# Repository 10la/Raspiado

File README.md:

## Raspiado

A USB hub that fits in the space and footprint of the existing Raspberry Pi.  Compatible with the RPi B, RPi B+, and RPi 2.

Power your Pi, add USB ports, and look great doing it!

******************
### File Descriptions
[4PxU_RPISB Specification.docx](https://github.com/10la/Raspiado/blob/master/4PxU_RPISB%20Specification.docx) is the hardware specification document created by Mindlab Tech for Raspiado.  It represents a formalized document that governs what functions and requirements Raspiado needed and how those things would be achieved.

[PCB Design Files](https://github.com/10la/Raspiado/tree/master/PCB%20Design%20Files) are the EAGLE files for the Raspiado board.

It includes 2 folders- the main design files are in [4PxU_RPi Rev B 18July2014](https://github.com/10la/Raspiado/tree/master/PCB%20Design%20Files/4PxU_RPi%20Rev%20B%2018July2014).  I had a small issue with the board logo and the resulting change are stored in [2014-10-3 new logo](https://github.com/10la/Raspiado/tree/master/PCB%20Design%20Files/2014-10-3%20new%20logo)

When I went to production with Raspiado, I required a few crossreferenced components in order to function with the inventory items that my PCB manufacturer preferred.  You can find those in the [BOM_Crossreferences](https://github.com/10la/Raspiado/blob/master/PCB%20Design%20Files/BOM_Raspiado_V1P4_crossreferences.xlsx) spreadsheet.

******************
### Kickstarter

Raspiado would have never seen the light of day with it's attractive, intelligent, and supportive backers.

When I started the project, I never knew that I'd be able to create something that would be appreciated by people all over the world.

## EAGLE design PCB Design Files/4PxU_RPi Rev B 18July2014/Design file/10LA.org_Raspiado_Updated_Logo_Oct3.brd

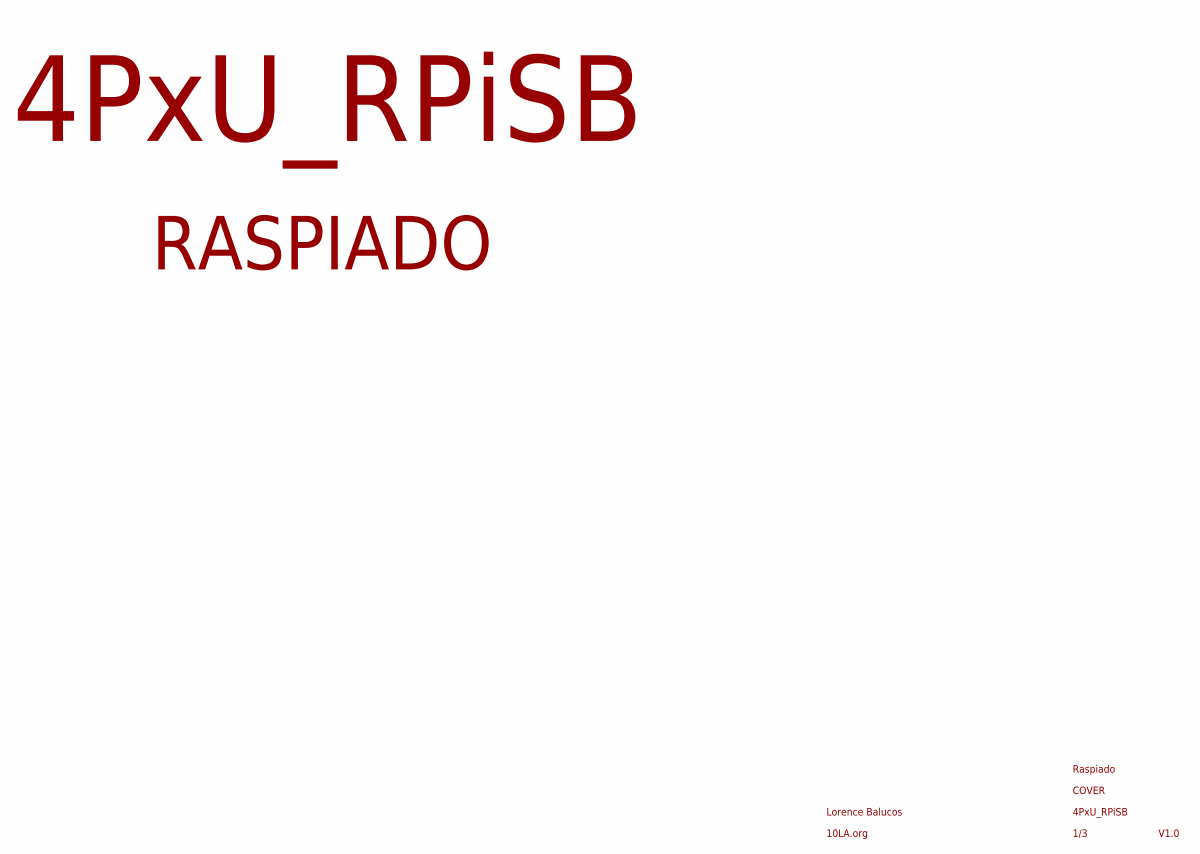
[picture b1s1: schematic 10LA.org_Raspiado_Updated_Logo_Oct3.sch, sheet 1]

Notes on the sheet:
1/3
4PxU_RPiSB
V1.0
10LA.org
RASPIADO
COVER
Lorence Balucos
Raspiado

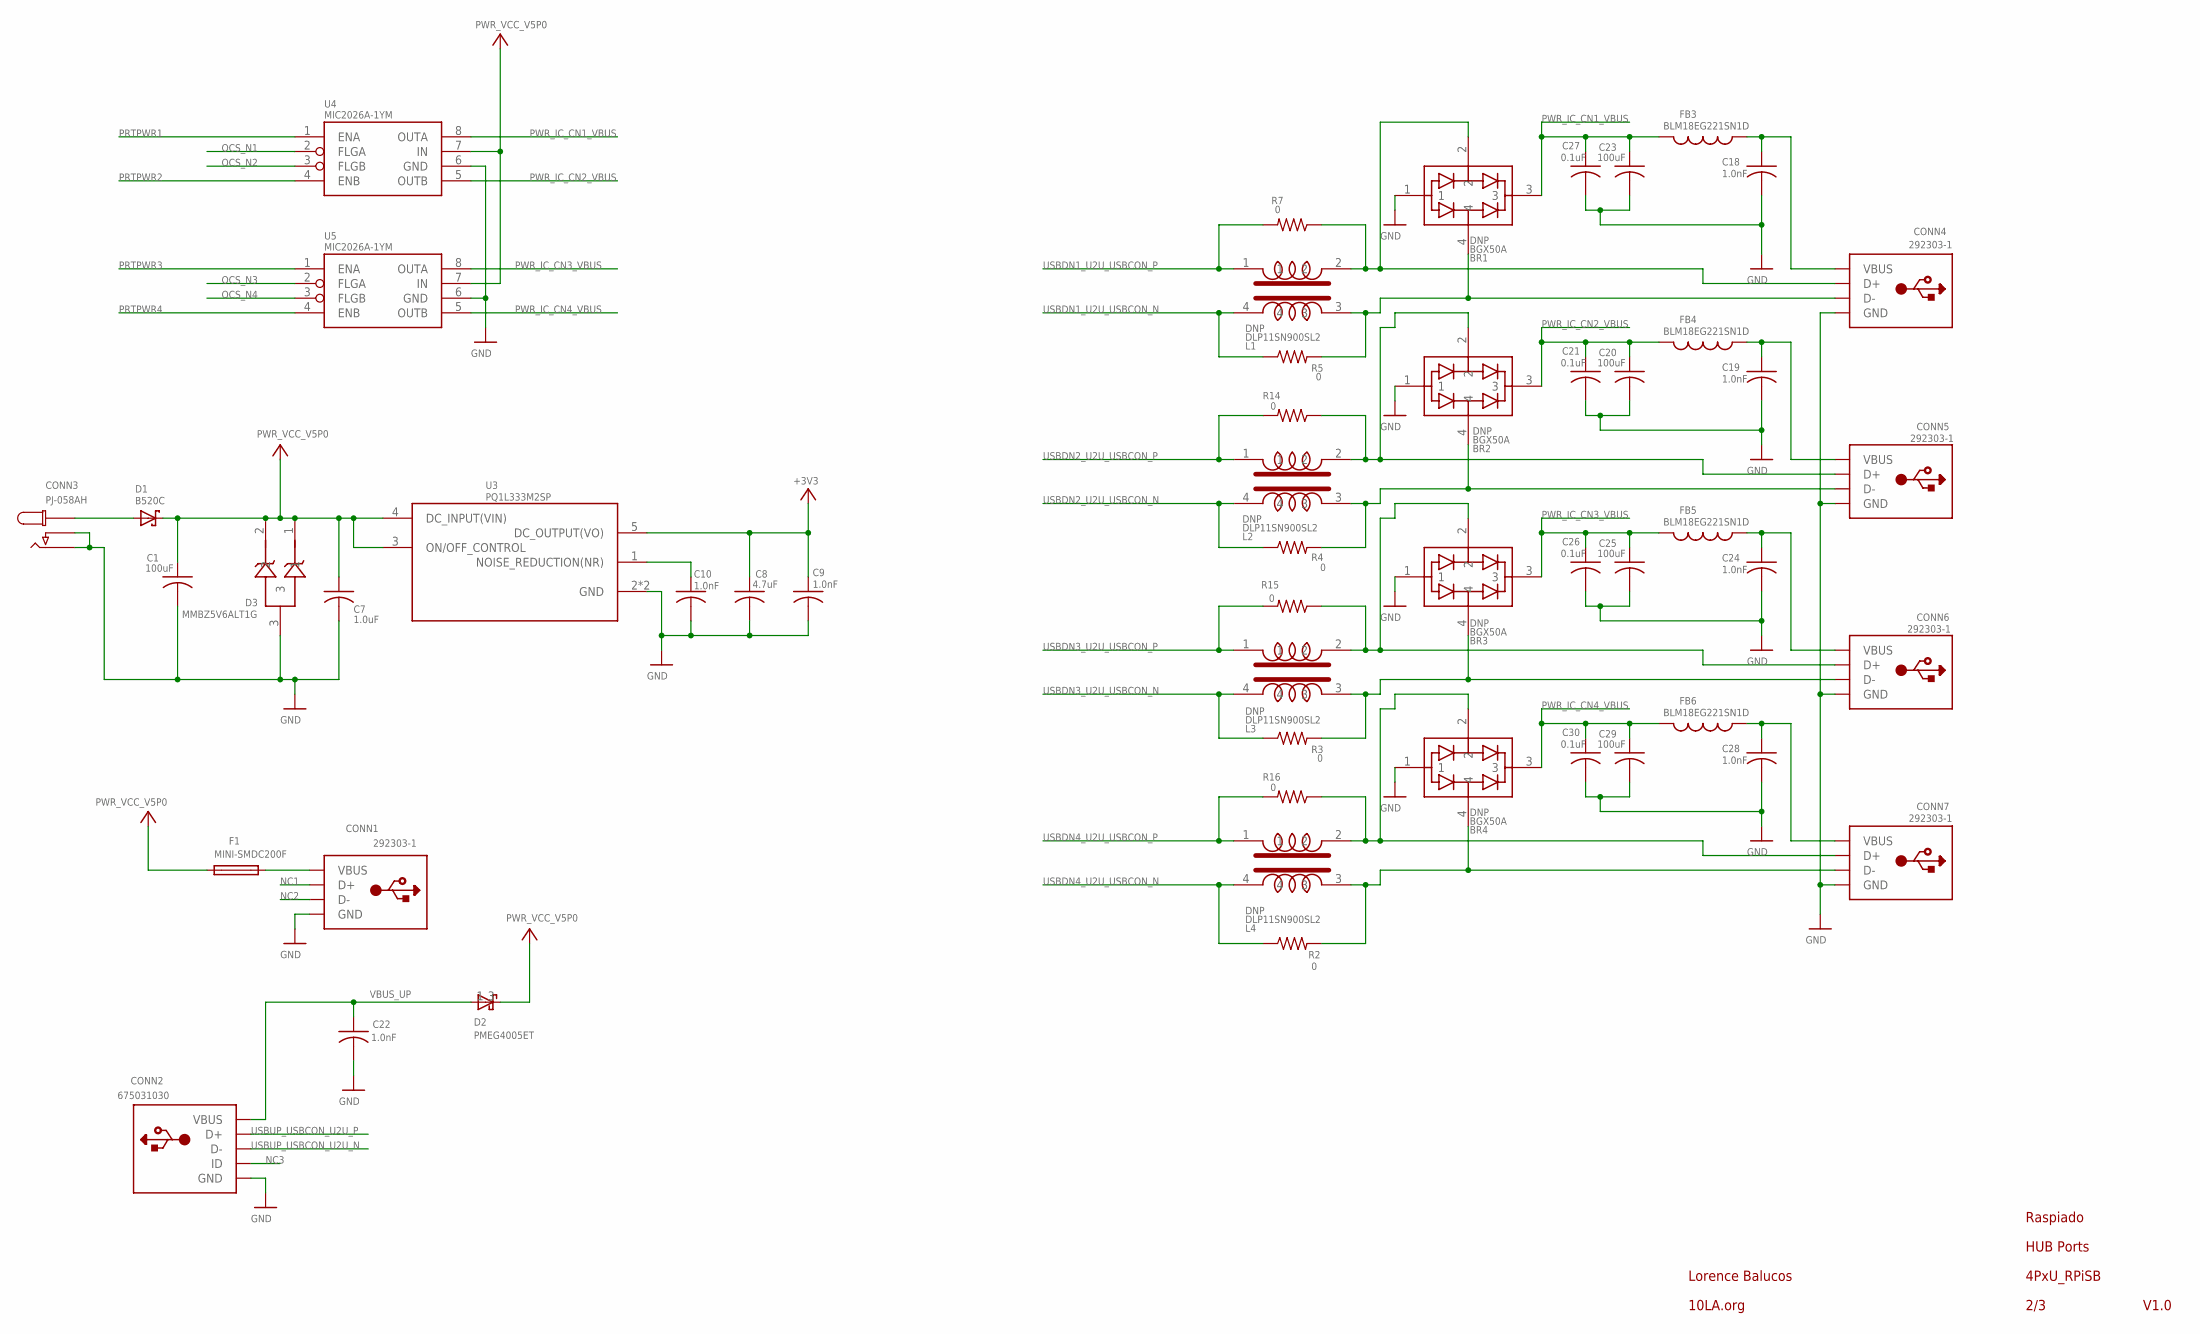
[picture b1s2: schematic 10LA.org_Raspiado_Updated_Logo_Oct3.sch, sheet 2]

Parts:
BR1, BR2, BR3, BR4: BGX50A; SOT-143
C1, C20, C23, C25, C29: 100uF; RADIAL_SMT
C7: 1.0uF; C0603
C8: 4.7uF; C0603
C9, C10, C18, C19, C22, C24, C28: 1.0nF; 0402
C21, C26, C27, C30: 0.1uF; 0402
CONN1, CONN4, CONN5, CONN6, CONN7: 292303-1; STYLEA,RIGHTANGLE,THROUGH-HOLE
CONN2: 675031030; MINI_B
CONN3: PJ-058AH
D1: B520C
D2: PMEG4005ET; SOT23
D3: MMBZ5V6ALT1G; SOT23
F1: MINI-SMDC200F
FB3, FB4, FB5, FB6: BLM18EG221SN1D; C0603
L1, L2, L3, L4: DLP11SN900SL2; 0504
R2, R3, R4, R5, R7, R14, R15, R16: 0; R0402
U3: PQ1L333M2SP
U4, U5: MIC2026A-1YM; SO_08

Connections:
+3V3: C8.1, C9.1, U3.5 (DC_OUTPUT(VO)); also elsewhere on the board
GND: BR1.1, BR2.1, BR3.1, BR4.1, C1.- (2), C7.2, C8.2, C9.2, C10.2, C18.2, C19.2, C20.- (2), C21.2, C22.2, C23.- (2), C24.2, C25.- (2), C26.2, C27.2, C28.2, C29.- (2), C30.2, CONN1.GND, CONN1.GND1 (GND), CONN1.GND2 (GND), CONN2.GND, CONN2.GND1 (GND), CONN2.GND2 (GND), CONN2.GND3 (GND), CONN2.GND4 (GND), CONN3.2, CONN3.3, CONN4.GND, CONN4.GND1 (GND), CONN4.GND2 (GND), CONN5.GND, CONN5.GND1 (GND), CONN5.GND2 (GND), CONN6.GND, CONN6.GND1 (GND), CONN6.GND2 (GND), CONN7.GND, CONN7.GND1 (GND), CONN7.GND2 (GND), D3.3, U3.2 (GND), U3.P$3 (GND), U4.6 (GND), U5.6 (GND); also elsewhere on the board
unnamed: C19.1, CONN5.VBUS, FB4.1
unnamed: BR2.2, CONN5.SIG2 (D+), L2.2, R14.1
unnamed: CONN3.1, D1.P$1 (1)
unnamed: C10.1, U3.1 (NOISE_REDUCTION(NR))
unnamed: C18.1, CONN4.VBUS, FB3.1
unnamed: BR1.2, CONN4.SIG2 (D+), L1.2, R7.1
unnamed: CONN1.VBUS, F1.2
unnamed: C24.1, CONN6.VBUS, FB5.1
unnamed: BR3.2, CONN6.SIG2 (D+), L3.2, R15.1
unnamed: C28.1, CONN7.VBUS, FB6.1
unnamed: BR4.2, CONN7.SIG2 (D+), L4.2, R16.1
NC1: CONN1.SIG2 (D+)
NC2: CONN1.SIG1 (D-)
NC3: CONN2.ID
OCS_N1: U4.2 (FLGA); also elsewhere on the board
OCS_N2: U4.3 (FLGB); also elsewhere on the board
OCS_N3: U5.2 (FLGA); also elsewhere on the board
OCS_N4: U5.3 (FLGB); also elsewhere on the board
PRTPWR1: U4.1 (ENA); also elsewhere on the board
PRTPWR2: U4.4 (ENB); also elsewhere on the board
PRTPWR3: U5.1 (ENA); also elsewhere on the board
PRTPWR4: U5.4 (ENB); also elsewhere on the board
PWR_IC_CN1_VBUS: BR1.3, C23.+ (1), C27.1, FB3.2, U4.8 (OUTA)
PWR_IC_CN2_VBUS: BR2.3, C20.+ (1), C21.1, FB4.2, U4.5 (OUTB)
PWR_IC_CN3_VBUS: BR3.3, C25.+ (1), C26.1, FB5.2, U5.8 (OUTA)
PWR_IC_CN4_VBUS: BR4.3, C29.+ (1), C30.1, FB6.2, U5.5 (OUTB)
USBDN1_U2U_USBCON_N: L1.4, R5.1; also elsewhere on the board
USBDN1_U2U_USBCON_P: L1.1, R7.2; also elsewhere on the board
USBDN1_U2U_USBCON_P2: BR4.4, CONN7.SIG1 (D-), L4.3, R2.2
USBDN1_U2U_USBCON_P3: BR3.4, CONN6.SIG1 (D-), L3.3, R3.2
USBDN1_U2U_USBCON_P4: BR2.4, CONN5.SIG1 (D-), L2.3, R4.2
USBDN1_U2U_USBCON_P5: BR1.4, CONN4.SIG1 (D-), L1.3, R5.2
USBDN2_U2U_USBCON_N: L2.4, R4.1; also elsewhere on the board
USBDN2_U2U_USBCON_P: L2.1, R14.2; also elsewhere on the board
USBDN3_U2U_USBCON_N: L3.4, R3.1; also elsewhere on the board
USBDN3_U2U_USBCON_P: L3.1, R15.2; also elsewhere on the board
USBDN4_U2U_USBCON_N: L4.4, R2.1; also elsewhere on the board
USBDN4_U2U_USBCON_P: L4.1, R16.2; also elsewhere on the board
USBUP_USBCON_U2U_N: CONN2.D-; also elsewhere on the board
USBUP_USBCON_U2U_P: CONN2.D+; also elsewhere on the board
VBUS_UP: C22.1, CONN2.VBUS, D2.1; also elsewhere on the board
VCC: C1.+ (1), C7.1, D1.P$2 (3), D2.3, D3.1, D3.2, F1.1, U3.3 (ON/OFF_CONTROL), U3.4 (DC_INPUT(VIN)), U4.7 (IN), U5.7 (IN)

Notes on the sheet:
2/3
V1.0
Lorence Balucos
10LA.org
Raspiado
4PxU_RPiSB
HUB Ports

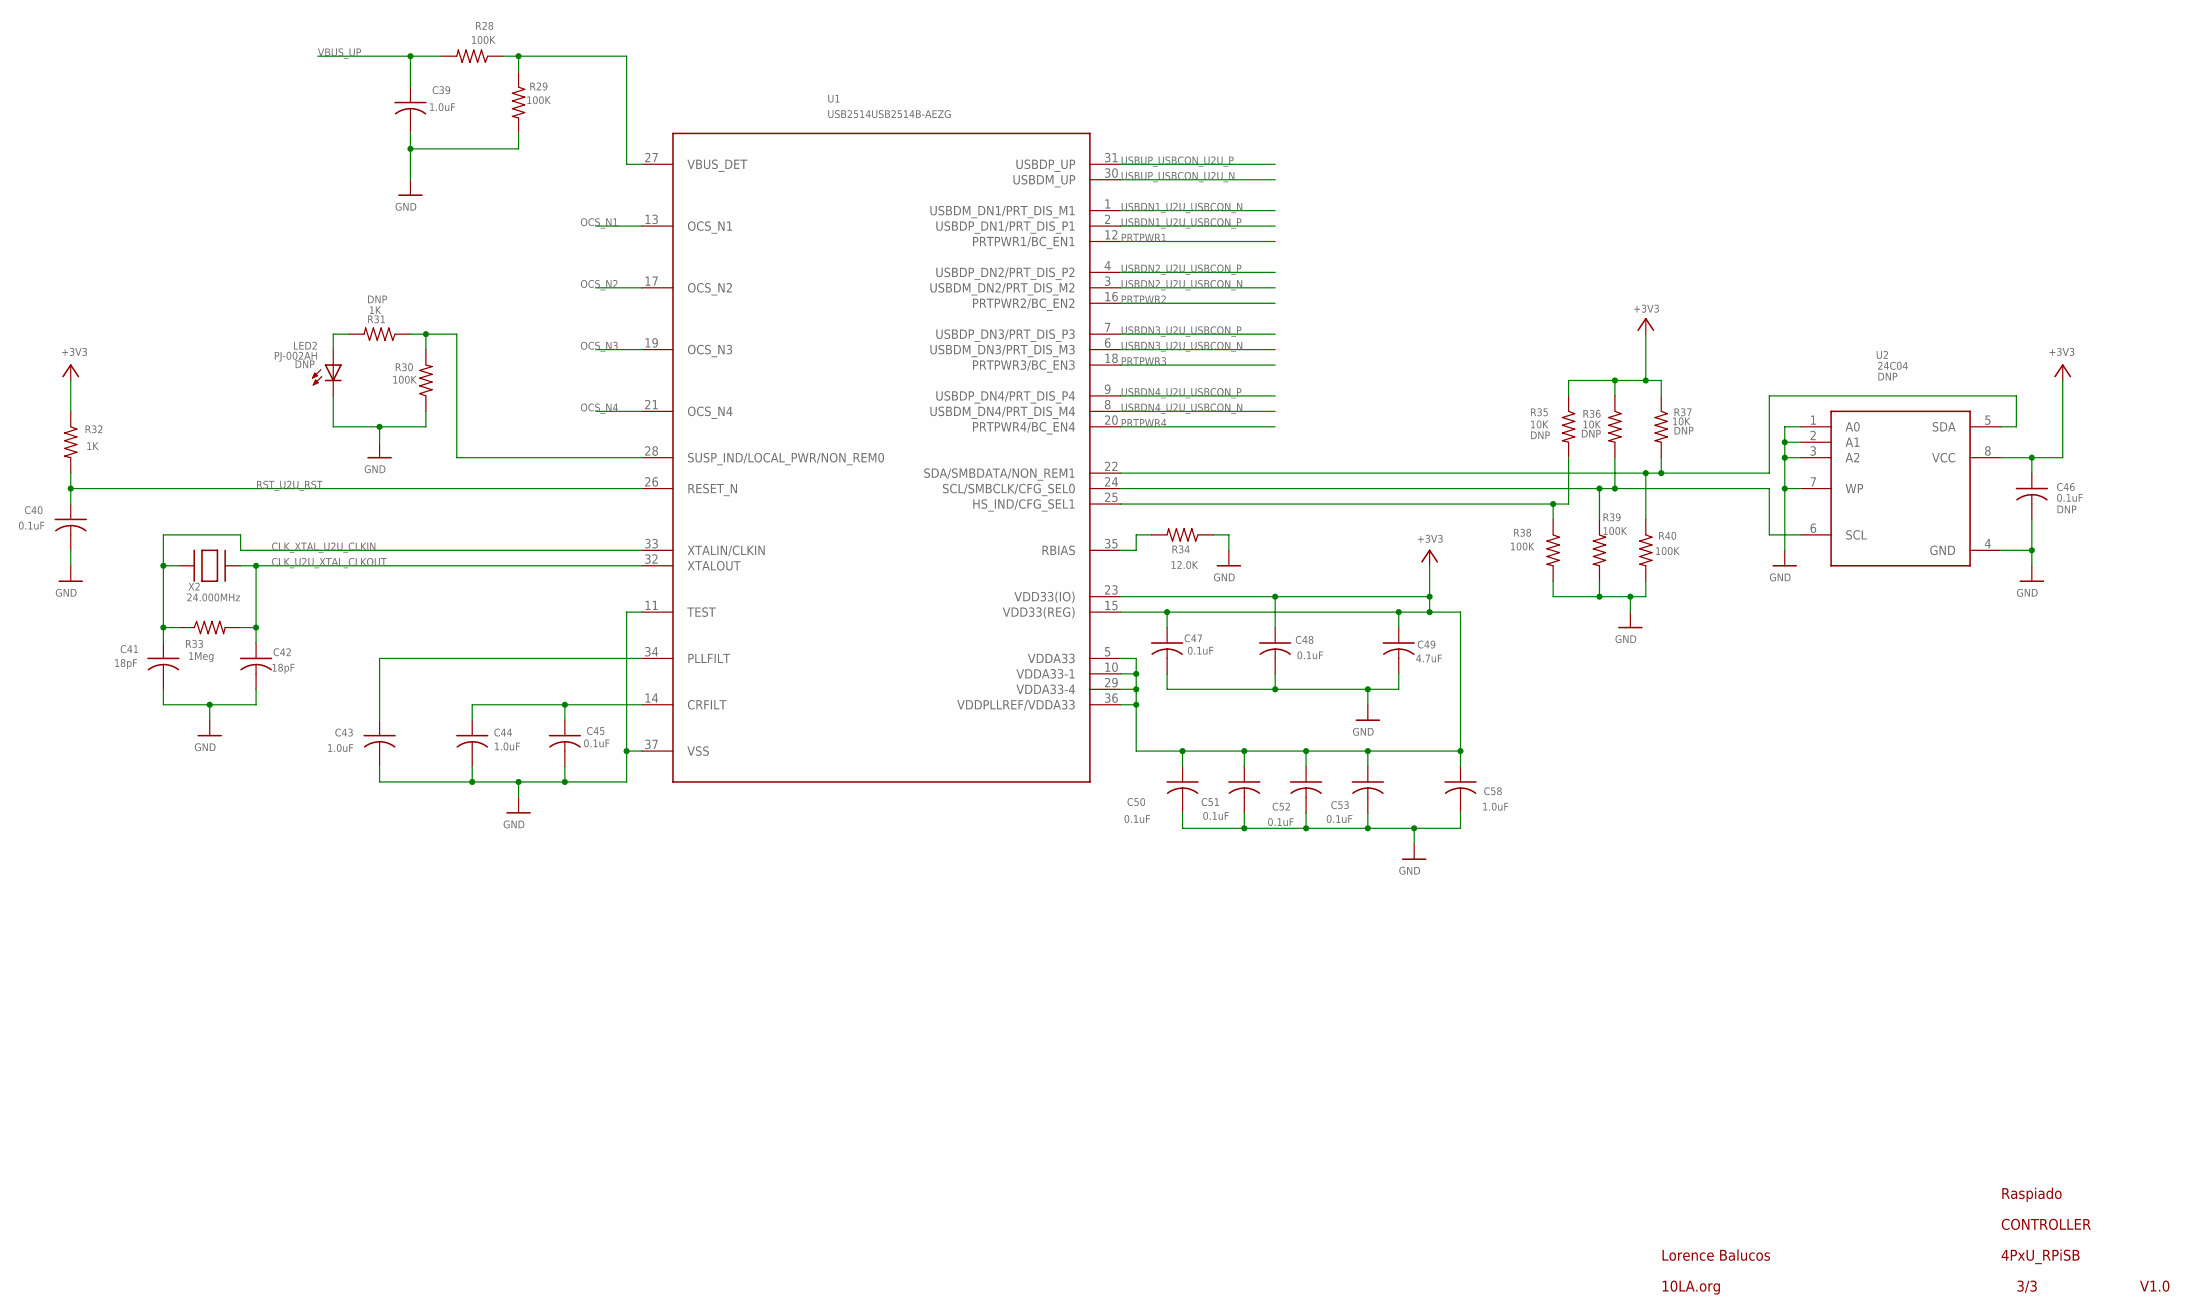
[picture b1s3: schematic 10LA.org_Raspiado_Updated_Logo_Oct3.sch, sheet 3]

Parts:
C39, C58: 1.0uF; C0603
C40, C45, C46, C47, C48, C50, C51, C52, C53: 0.1uF; 0402
C41, C42: 18pF; 0402
C43, C44: 1.0uF; 0402
C49: 4.7uF; C0603
LED2: PJ-002AH; 0603
R28, R29, R30, R38, R39, R40: 100K; R0603
R31, R32: 1K; R0603
R33: 1Meg; R0603
R34: 12.0K; R0603
R35, R36, R37: 10K; R0603
U1: USB2514USB2514B-AEZG; QFN36
U2: 24C04; SO-8
X2: 24.000MHz; HC-49SMT

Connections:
+3V3: C46.1, C47.1, C48.1, C49.1, C50.1, C51.1, C52.1, C53.1, C58.1, R32.1, R35.1, R36.1, R37.1, U1.5 (VDDA33), U1.10 (VDDA33-1), U1.15 (VDD33(REG)), U1.23 (VDD33(IO)), U1.29 (VDDA33-4), U1.36 (VDDPLLREF/VDDA33), U2.8 (VCC); also elsewhere on the board
CLK_U2U_XTAL_CLKOUT: C42.1, R33.2, U1.32 (XTALOUT), X2.2
CLK_XTAL_U2U_CLKIN: C41.1, R33.1, U1.33 (XTALIN/CLKIN), X2.1
CRFILT: C44.1, C45.1, U1.14 (CRFILT)
GND: C39.2, C40.2, C41.2, C42.2, C43.2, C44.2, C45.2, C46.2, C47.2, C48.2, C49.2, C50.2, C51.2, C52.2, C53.2, C58.2, LED2.C, R29.2, R30.1, R34.1, R38.2, R39.2, R40.2, U1.11 (TEST), U1.37 (VSS), U2.1 (A0), U2.2 (A1), U2.3 (A2), U2.4 (GND), U2.7 (WP); also elsewhere on the board
unnamed: LED2.A, R31.2
OCS_N1: U1.13 (OCS_N1); also elsewhere on the board
OCS_N2: U1.17 (OCS_N2); also elsewhere on the board
OCS_N3: U1.19 (OCS_N3); also elsewhere on the board
OCS_N4: U1.21 (OCS_N4); also elsewhere on the board
PLLFILT: C43.1, U1.34 (PLLFILT)
PRTPWR1: U1.12 (PRTPWR1/BC_EN1); also elsewhere on the board
PRTPWR2: U1.16 (PRTPWR2/BC_EN2); also elsewhere on the board
PRTPWR3: U1.18 (PRTPWR3/BC_EN3); also elsewhere on the board
PRTPWR4: U1.20 (PRTPWR4/BC_EN4); also elsewhere on the board
RBIAS: R34.2, U1.35 (RBIAS)
REM0: R30.2, R31.1, U1.28 (SUSP_IND/LOCAL_PWR/NON_REM0)
REM1: R37.2, R40.1, U1.22 (SDA/SMBDATA/NON_REM1), U2.5 (SDA)
RST_U2U_RST: C40.1, R32.2, U1.26 (RESET_N)
SCL: R36.2, R39.1, U1.24 (SCL/SMBCLK/CFG_SEL0), U2.6 (SCL)
SEL1: R35.2, R38.1, U1.25 (HS_IND/CFG_SEL1)
USBDN1_U2U_USBCON_N: U1.1 (USBDM_DN1/PRT_DIS_M1); also elsewhere on the board
USBDN1_U2U_USBCON_P: U1.2 (USBDP_DN1/PRT_DIS_P1); also elsewhere on the board
USBDN2_U2U_USBCON_N: U1.3 (USBDM_DN2/PRT_DIS_M2); also elsewhere on the board
USBDN2_U2U_USBCON_P: U1.4 (USBDP_DN2/PRT_DIS_P2); also elsewhere on the board
USBDN3_U2U_USBCON_N: U1.6 (USBDM_DN3/PRT_DIS_M3); also elsewhere on the board
USBDN3_U2U_USBCON_P: U1.7 (USBDP_DN3/PRT_DIS_P3); also elsewhere on the board
USBDN4_U2U_USBCON_N: U1.8 (USBDM_DN4/PRT_DIS_M4); also elsewhere on the board
USBDN4_U2U_USBCON_P: U1.9 (USBDP_DN4/PRT_DIS_P4); also elsewhere on the board
USBUP_USBCON_U2U_N: U1.30 (USBDM_UP); also elsewhere on the board
USBUP_USBCON_U2U_P: U1.31 (USBDP_UP); also elsewhere on the board
VBUS_UP: C39.1, R28.2; also elsewhere on the board
VBUS_UPSTREAM: R28.1, R29.1, U1.27 (VBUS_DET)

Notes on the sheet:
4PxU_RPiSB
3/3
V1.0
Lorence Balucos
10LA.org
Raspiado
CONTROLLER

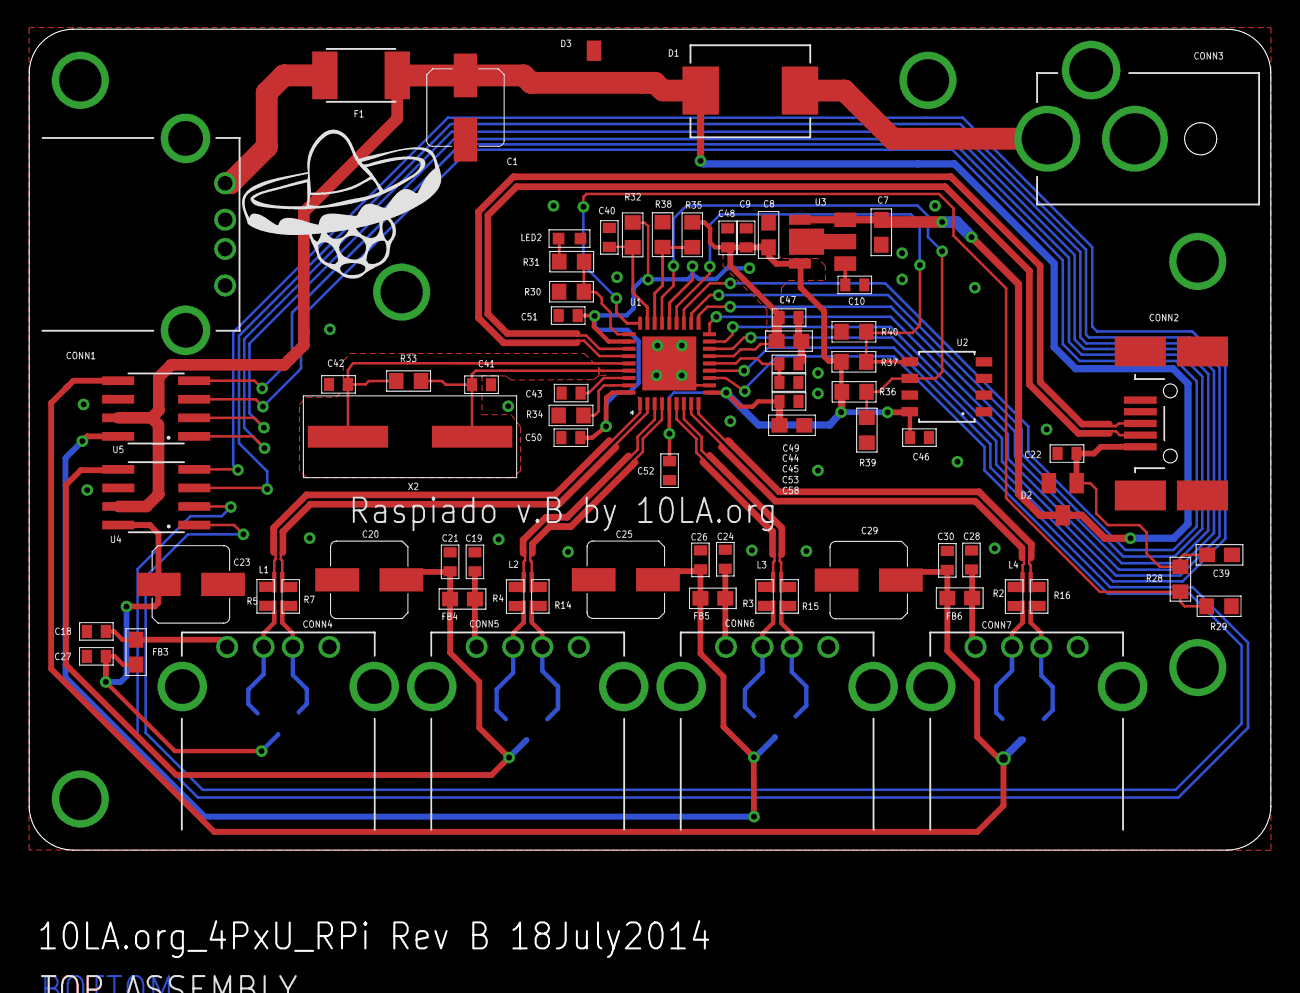
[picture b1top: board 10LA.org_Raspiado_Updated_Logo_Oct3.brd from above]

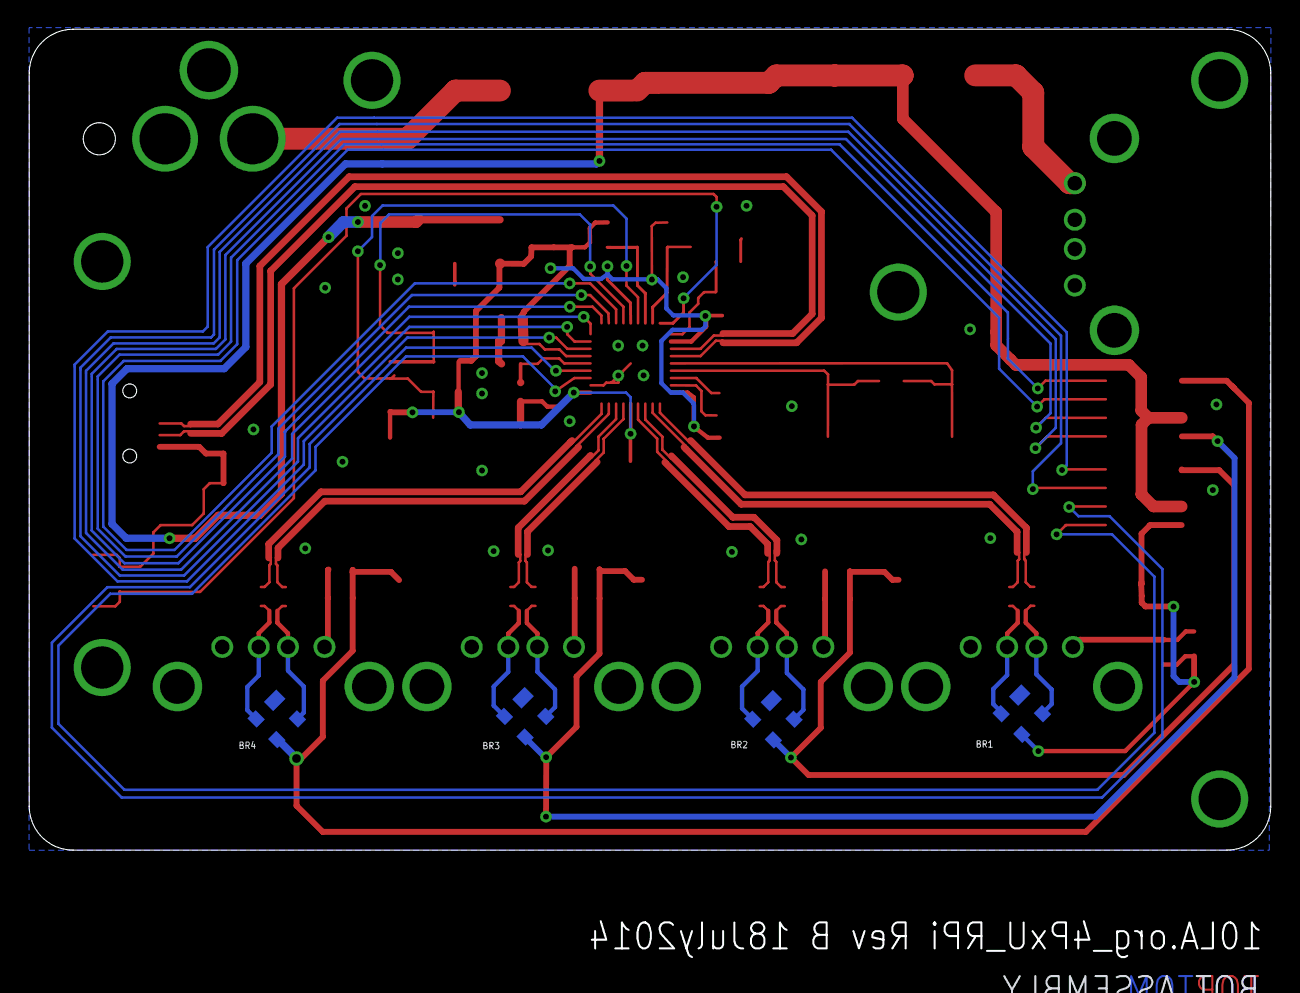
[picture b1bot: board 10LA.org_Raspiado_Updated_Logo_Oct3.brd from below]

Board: 2 copper layers, 85.0 x 56.2 mm, 86 parts (4 on the bottom side), 53 nets.

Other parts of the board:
U$1: FRAME

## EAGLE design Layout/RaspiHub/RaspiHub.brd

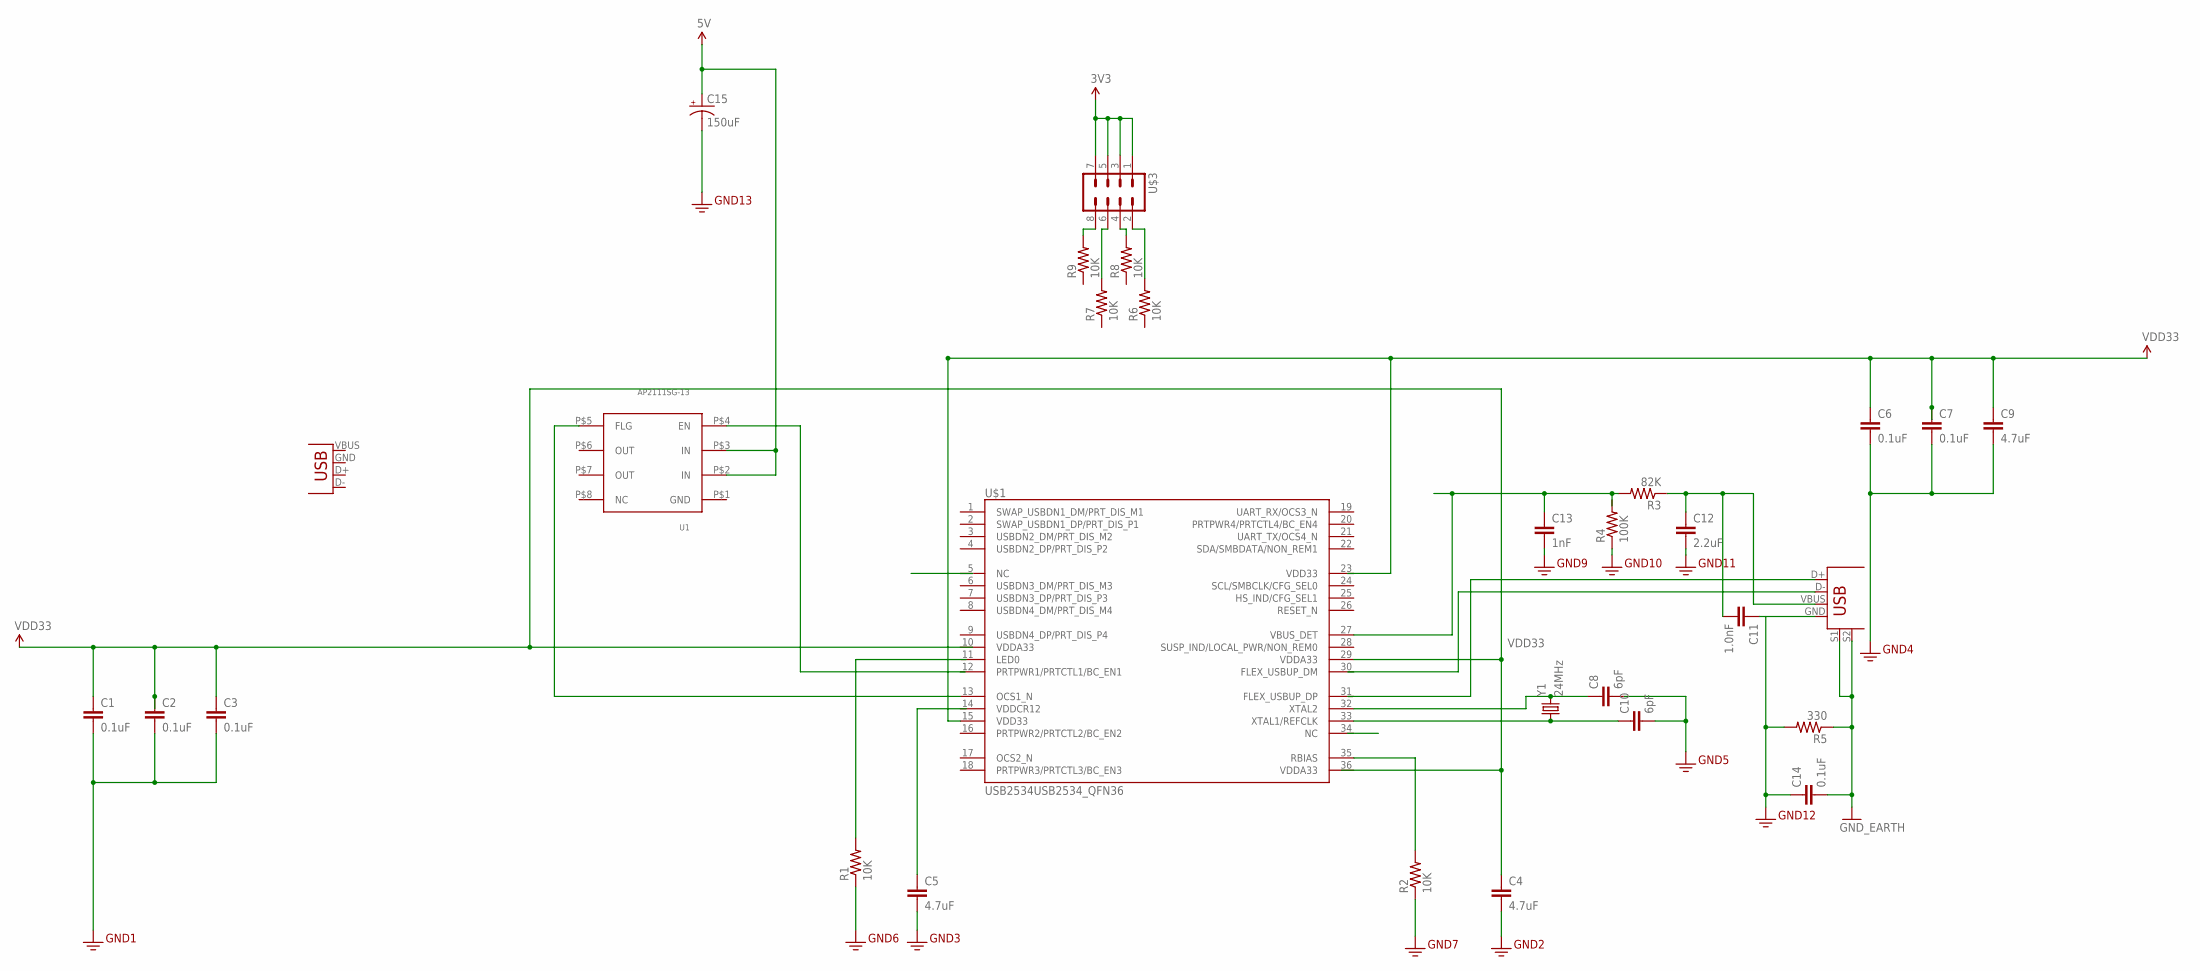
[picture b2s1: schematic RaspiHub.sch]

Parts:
C1, C2, C3, C6, C7: 0.1uF; 0402-CAP
C4, C5, C9: 4.7uF; 0603-CAP
C8, C10: 6pF; 0603-CAP
C11: 1.0nF; 0402-CAP
C12: 2.2uF; 0402-CAP
C13: 1nF; 0402-CAP
C14: 0.1uF; 0603-CAP
C15: 150uF; EIA3528
JP1: USB-A-H
R1, R2, R6, R7, R8, R9: 10K; 0603-RES
R3: 82K; 0603-RES
R4: 100K; 0603-RES
R5: 330; 0603-RES
U1: AP2111SG-13
U$1: USB2534USB2534_QFN36; USB2534
U$2: USB+SHIELD; USB-B-PTH
U$3: M04X2; 2X4
Y1: 24MHz; HC49U-V

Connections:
3.3V: C1.2, C2.2, C3.2, C4.2, C5.2, C6.2, C7.2, C8.2, C9.2, C10.2, C12.2, C13.2, C14.1, C15.C (-), R1.1, R2.1, R4.1, R5.2
GND: C14.2, R5.1, U1.P$1 (GND), U$2.S1, U$2.S2
unnamed: C10.1, U$1.33 (XTAL1/REFCLK), Y1.1
unnamed: C8.1, U$1.32 (XTAL2), Y1.2
unnamed: R2.2, U$1.35 (RBIAS)
unnamed: R7.2, U$3.6
unnamed: C11.2, C12.1, R3.1, U$2.VBUS
unnamed: C11.1, U$2.GND
unnamed: R9.2, U$3.8
unnamed: R8.2, U$3.4
unnamed: R6.2, U$3.2
unnamed: U1.P$5 (FLG), U$1.13 (OCS1_N)
VBUS_NET: C13.1, R3.2, U$1.27 (VBUS_DET)
VCC: C6.1, C7.1, C9.1, C15.A (+), U1.P$2 (IN), U1.P$3 (IN), U$1.15 (VDD33), U$3.1, U$3.3, U$3.5, U$3.7
VDD33: C1.1, C2.1, C3.1, U$1.23 (VDD33), U$1.29 (VDDA33)
VDDA33: U$1.36 (VDDA33)

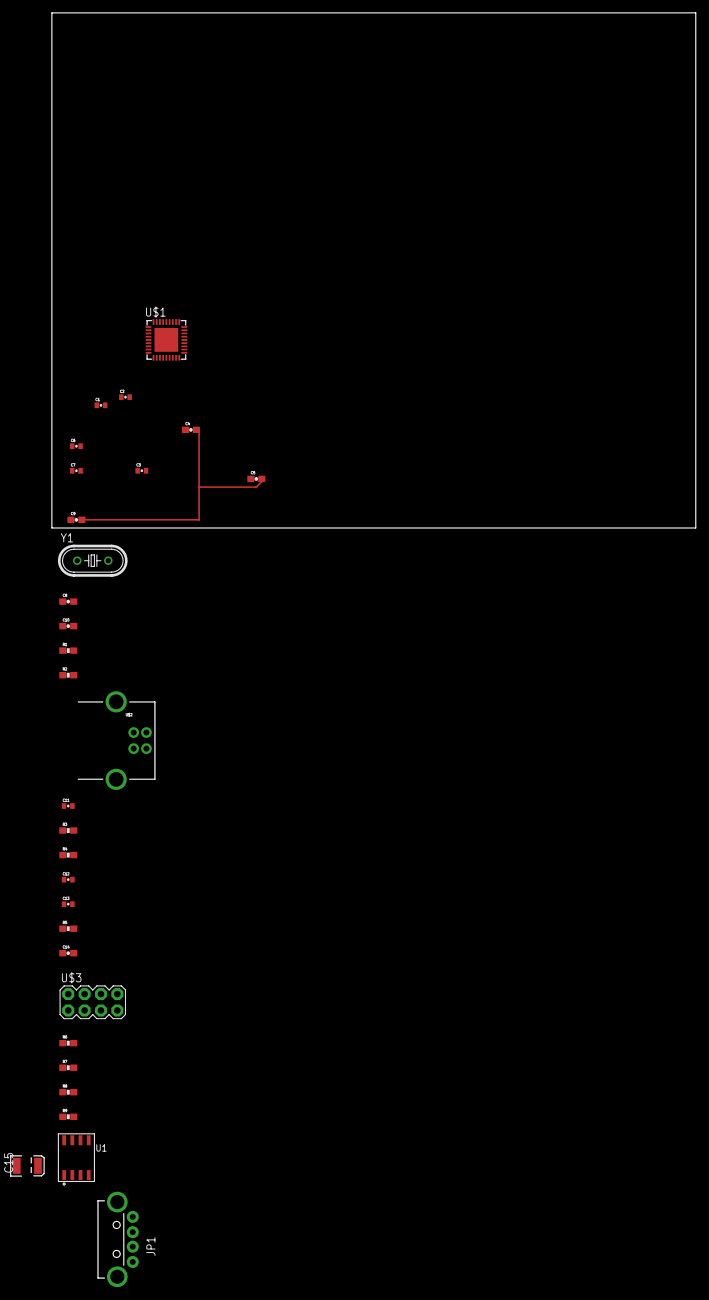
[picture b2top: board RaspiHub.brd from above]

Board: 2 copper layers, 100.0 x 80.0 mm, 30 parts (0 on the bottom side), 15 nets.

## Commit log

2018-03-11 ADD .gitignore
2018-03-12 Set theme jekyll-theme-cayman
2018-03-12 Update README for github pages
2018-03-12 Update README with Raspiado text
2018-03-13 ADD more media files
2018-03-13 RENAME design file folder
2018-03-16 ADD pics and text to README for PCB design files
2018-03-23 ADD kickstarter section
2018-03-23 Create CNAME

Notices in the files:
parts and their libraries:
SparkFun-Capacitors: Licensing: CC v3.0 Share-Alike You are welcome to use this library for commercial purposes.
